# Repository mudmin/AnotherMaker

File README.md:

# AnotherMaker
This is where I will store code snippets for AnotherMaker Videos

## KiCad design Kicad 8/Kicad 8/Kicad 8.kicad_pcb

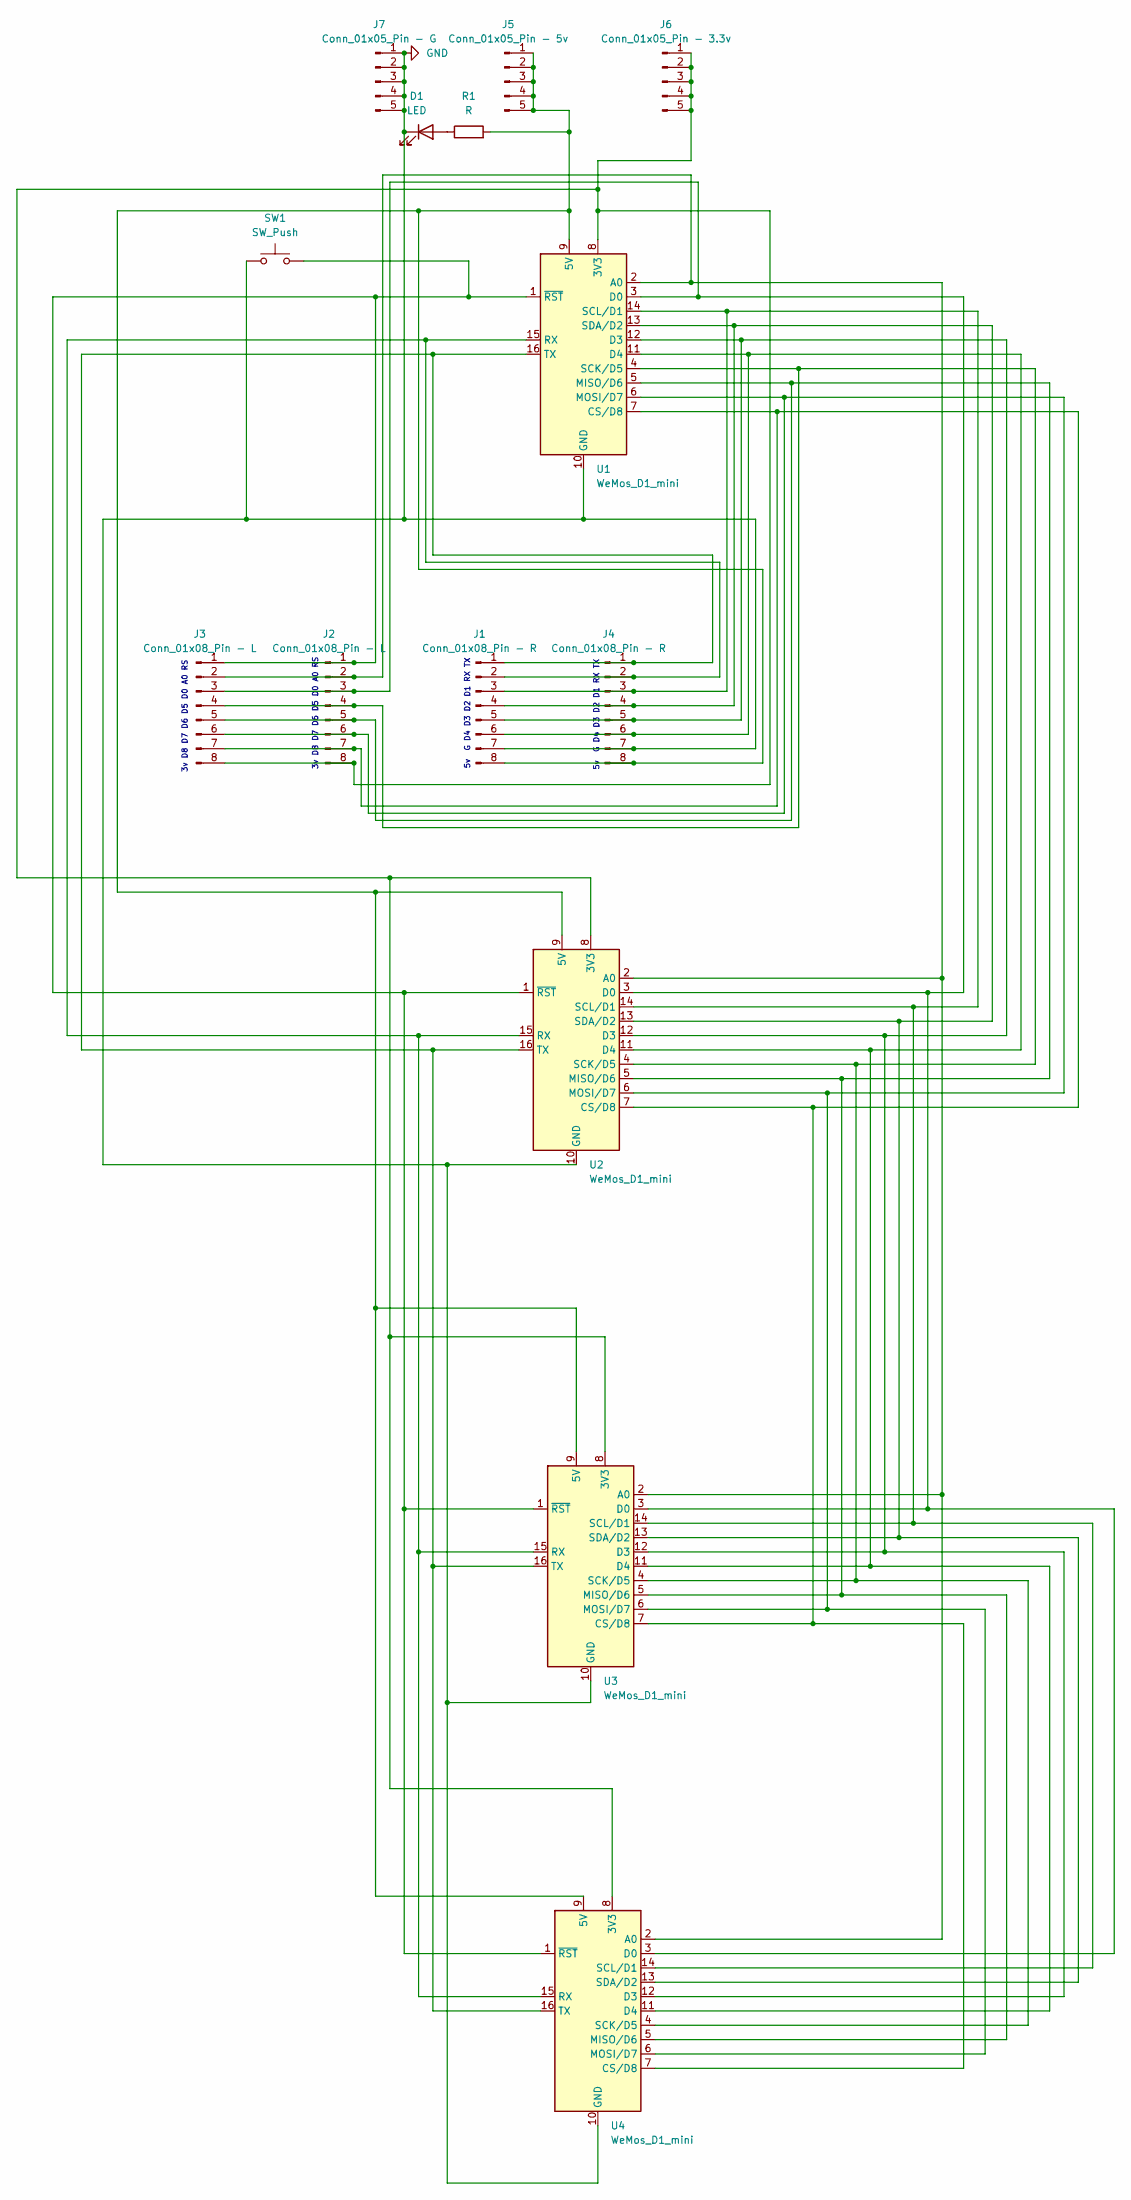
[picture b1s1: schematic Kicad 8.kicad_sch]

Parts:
D1: LED; LED_D3.0mm
J1: Conn_01x08_Pin - R; PinHeader_1x08_P2.54mm_Vertical
J2: Conn_01x08_Pin - L; PinHeader_1x08_P2.54mm_Vertical
J3: Conn_01x08_Pin - L; TerminalBlock_RND_205-00018_1x08_P5.00mm_Horizontal
J4: Conn_01x08_Pin - R; TerminalBlock_RND_205-00018_1x08_P5.00mm_Horizontal
J5: Conn_01x05_Pin - 5v; PinSocket_1x05_P2.54mm_Vertical
J6: Conn_01x05_Pin - 3.3v; PinSocket_1x05_P2.54mm_Vertical
J7: Conn_01x05_Pin - G; PinSocket_1x05_P2.54mm_Vertical
R1: R; R_Axial_DIN0207_L6.3mm_D2.5mm_P7.62mm_Horizontal
SW1: SW_Push; SW_PUSH_6mm_H5mm
U1, U2, U3, U4: WeMos_D1_mini; WEMOS_D1_mini_light

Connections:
GND: D1.1 (K), J1.7, J4.7, J7.1, J7.2, J7.3, J7.4, J7.5, SW1.1, U1.10 (GND), U2.10 (GND), U3.10 (GND), U4.10 (GND)
unnamed: D1.2 (A), R1.1
unnamed: J1.1, J4.1, U1.16 (TX), U2.16 (TX), U3.16 (TX), U4.16 (TX)
unnamed: J1.2, J4.2, U1.15 (RX), U2.15 (RX), U3.15 (RX), U4.15 (RX)
unnamed: J1.3, J4.3, U1.14 (SCL/D1), U2.14 (SCL/D1), U3.14 (SCL/D1), U4.14 (SCL/D1)
unnamed: J1.4, J4.4, U1.13 (SDA/D2), U2.13 (SDA/D2), U3.13 (SDA/D2), U4.13 (SDA/D2)
unnamed: J1.5, J4.5, U1.12 (D3), U2.12 (D3), U3.12 (D3), U4.12 (D3)
unnamed: J1.6, J4.6, U1.11 (D4), U2.11 (D4), U3.11 (D4), U4.11 (D4)
unnamed: J1.8, J4.8, J5.1, J5.2, J5.3, J5.4, J5.5, R1.2, U1.9 (5V), U2.9 (5V), U3.9 (5V), U4.9 (5V)
unnamed: J2.1, J3.1, SW1.2, U1.1 (~RST), U2.1 (~RST), U3.1 (~RST), U4.1 (~RST)
unnamed: J2.2, J3.2, U1.2 (A0), U2.2 (A0), U3.2 (A0), U4.2 (A0)
unnamed: J2.3, J3.3, U1.3 (D0), U2.3 (D0), U3.3 (D0), U4.3 (D0)
unnamed: J2.4, J3.4, U1.4 (SCK/D5), U2.4 (SCK/D5), U3.4 (SCK/D5), U4.4 (SCK/D5)
unnamed: J2.5, J3.5, U1.5 (MISO/D6), U2.5 (MISO/D6), U3.5 (MISO/D6), U4.5 (MISO/D6)
unnamed: J2.6, J3.6, U1.6 (MOSI/D7), U2.6 (MOSI/D7), U3.6 (MOSI/D7), U4.6 (MOSI/D7)
unnamed: J2.7, J3.7, U1.7 (CS/D8), U2.7 (CS/D8), U3.7 (CS/D8), U4.7 (CS/D8)
unnamed: J2.8, J3.8, J6.1, J6.2, J6.3, J6.4, J6.5, U1.8 (3V3), U2.8 (3V3), U3.8 (3V3), U4.8 (3V3)

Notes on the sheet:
3v D8 D7 D6 D5 D0 A0 RS
5v G D4 D3 D2 D1 RX TX

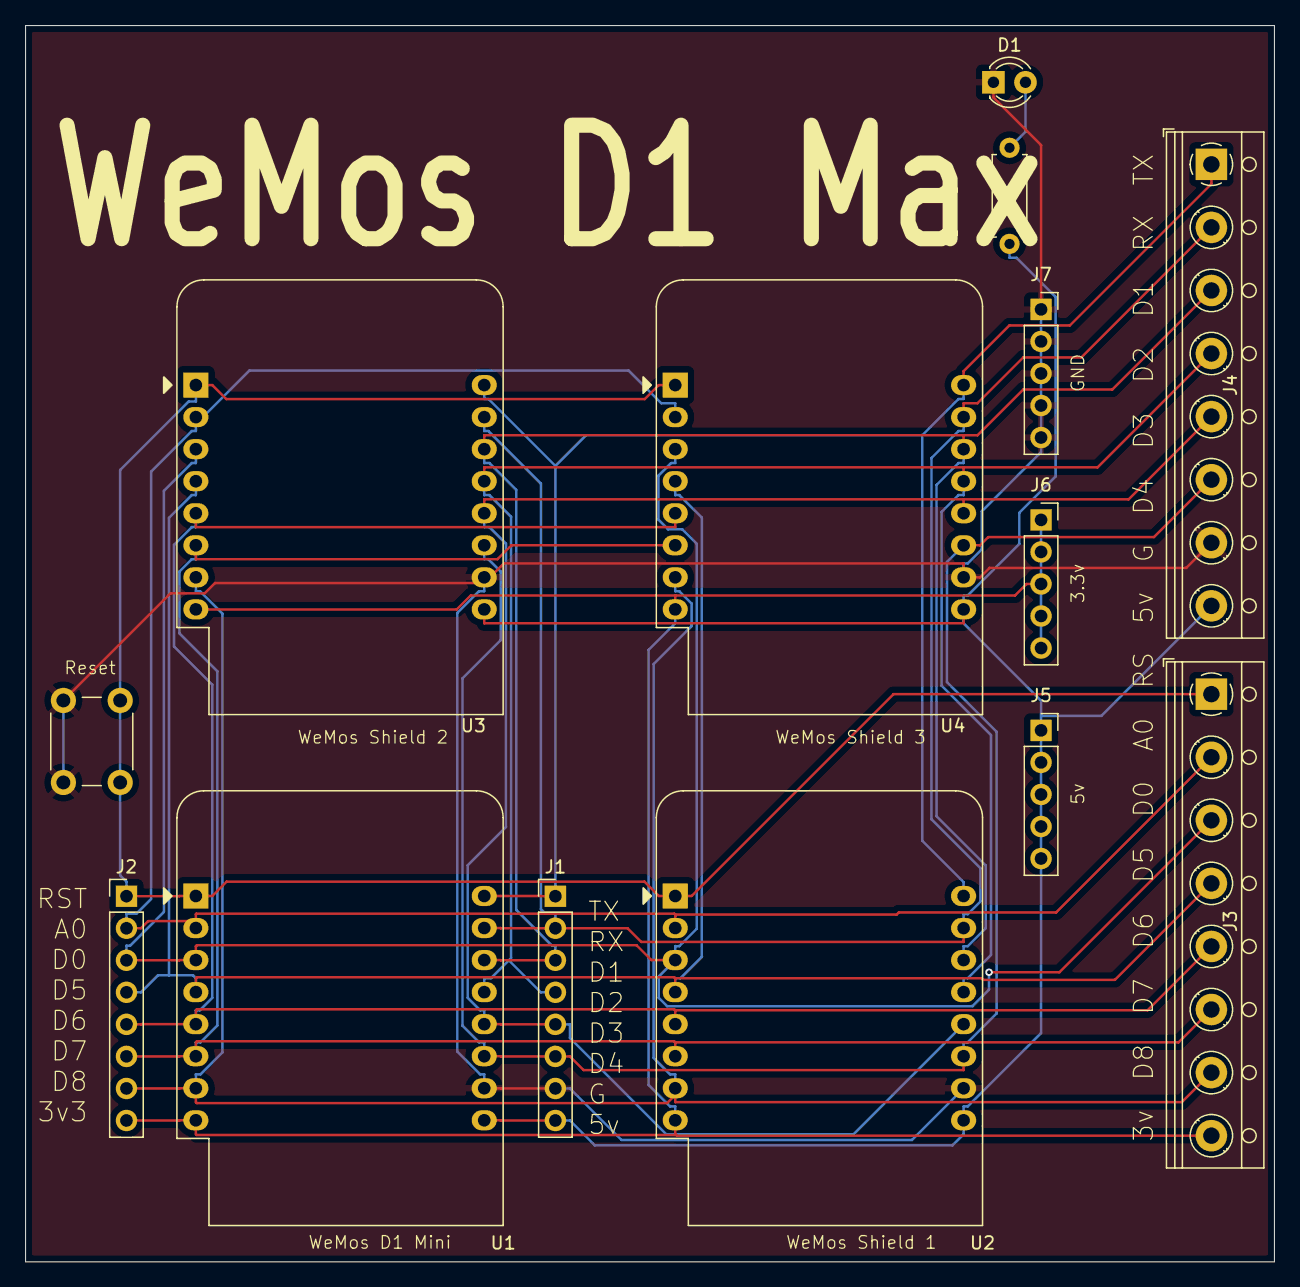
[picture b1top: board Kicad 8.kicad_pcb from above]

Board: 2 copper layers, 99.0 x 98.0 mm, 14 parts (0 on the bottom side), 17 nets.

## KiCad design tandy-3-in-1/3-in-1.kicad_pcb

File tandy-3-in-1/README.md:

# Credit where credit is due
This is forked from https://github.com/rkrenicki/Tandy-EX-HX-3in1 and this repo is primarily here in case his goes away for some reason.

# Tandy 1000 EX/HX 3-in-1 Expansion Board

This is a single expansion board designed for the Tandy 1000 EX and HX computers, to include the following upgrades:

* 640KB Base System Memory
* 96KB Upper Memory
* 16550-based DE9 Serial RS232 Port
* XT-IDE based CompactFlash "Hard Drive"

## Prerequisites

This board is for the Tandy 1000EX and 1000HX computers only.  It will not work in any other computer model as it is.
You must remove any expansion cards already in the computer, this is designed to be a single-board upgrade and has no provisions to allow for any other expansion cards.

## Installing

This board plugs into the Tandy PLUS interface, and takes up "Slot 2" on the rear of the computer.  Please be careful to align the PLUS bus connector before pushing down, to avoid bending pins on the computer.  Secure the backplate to the computer with two screws.
The IDE BIOS will automatically start and boot directly to the CF card on 1000EX machines.   1000HX loads a boot menu by default, and you will need to press F4 to load the IDE BIOS.  If you want to bypass the Tandy DOS ROM and boot menu, run "SETUPHX" and change the "Primary Start-up Device" to "DISK" and press F1 to save.

## Technical Details

This board has no configuration jumpers and is designed to be plug-and-play.  The only jumper is to enable programming the ROM.  Install the jumper to flash the XT-IDE BIOS, otherwise the jumper should be removed.  All assembled boards and kits sold by me come with a pre-programmed ROM, and this jumper should be left empty.

The board is hardwired with these memory locations/ports:
```
SRAM:  0x0000-0x5FFF, 0xC800-0xDFFF
UART:  0x3F8, IRQ 4
IDE:   0x300
ROM:   0xC000-0xC7FF
```

## Assembly Notes
All functions of the board are independent, no parts are shared between functions.  If you do not want to use a specific function, you can safely omit any parts referenced with the function in the name (such as "232" for RS232).

Recommended assembly order: (Shortest to tallest)
* 1  - Resistors (R1-R3, R4 for v1.8+)
* 2  - Bypass Capacitors (C1-C16, only noted as "0.1uF" on the boards)
* 3  - 74 series Chips (U1-4, U6-7, U9, U11-13)
* 4  - ROM Socket (U5 Socket)
* 5  - SRAM Chip (U10)
* 6  - Oscillator (OSC1)
* 7  - UART Socket (U8 Socket)  - Pay very special attention to the orientation!  See note below.
* 8  - Connectors (BUS1, CF-J1, CF-J2, 232-P2)
* 8a - Bodge Resistor on rear of board.  (Only for Version 1.7a boards)
* 9 -  ROM and UART chips into their sockets.
* 10  - CF Adapter
* 11 - Backplate

NOTE:  Please take careful note of part orientation.  To optimize some trace routing, not all chips are oriented in the same direction.  232-U6, 232-U8, and RAM-U11 are all opposite oritentation than the other horizontal chips.  Installing these backwards will destroy the chips.   Pay special attention to 232-U8's socket, it must be installed with the "Pin 1 Arrow" installed facing towards the left of the board.  232-OSC1 is installed "upside down", with the squared corner facing the upper right.

## Bill of Materials
|Quantity |Ref(s)        |Mouser Part Number  |Digikey Part Number |Description                                                     
|-----|--------------|--------------------|--------------------|----------------------------------------------------------------
| 1   |BUS1          |200-CES13101SD<br><i><b>See Note2 Below</i>|SAM1084-31-ND<br><i><b>See Note2 Below</i>|2x31 2.54mm Header Socket
| 1   |CF-J1         |517-8540-4500PL| |2x20 2.54mm Header Socket, 11mm height.
| 4   |R1 through R4 |603-CFR-12JT-52-10K | |10kOhm Resistor
| 16  |C1 through C16|594-K104M15X7RF53L2 | |0.1uF Multilayer Ceramic Capacitor, 2.5mm Lead Spacing
| 1   |CP1           |647-RNU1C101MDS1    | |100uF 16V Polymer or Electrolytic Capacitor, 2.5mm Lead Spacing
| 1   |232-OSC1      |774-MXO45HS-3C-1.8  |110-MXO45HS-3C-1M843200-ND |1.8432Mhz 1/2-size Oscillator
| 1   |232-P2        |806-K22X-E9P-N-99   |2092-K22X-E9P-N-ND      |DE9 Male Right Angle Connector  
| 2   |232-P2 Screw  |571-5207953-3       |SFSO4401NR-ND           |Jackscrew for DE9 connector
| 1   |232-U6        |595-GD75232N        |296-GD75232N-ND         |GD75232N RS232 Driver
| 2   |232-U7, 232-U9|595-SN74LS138N      |296-1639-5-ND           |74LS138 3-to-8 Line Demux
| 1   |232-U8        |701-ST16C550CJ44TR-F|1016-1259-5-ND          |16550/16C550 UART in PLCC-44 Package
| 1   |232-U8 Socket |517-8444-11B1-RK-TP |3M4411B1-ND             |PLCC-44 Through Hole Socket
| 1   |CF-J2         |200-CES10101TD      | |1x2 2.54mm Header Socket
| 1   |CF-U1         |595-SN74LS139AN     |296-1640-5-ND           |74LS139 Dual 2-to-4 Demux
| 2   |CF-U2, ROM-U4 |595-SN74LS688N<br> or 595-SN74F521N      |296-1667-5-ND          |74LS688 or 74F521 8-bit Comparator
| 2   |CF-U3, RAM-U11|595-SN74LS245N      |296-1655-5-ND           |74LS245 Tri-state Bus Transciever
| 1   |RAM-U10       |913-AS6C4008-55PCN  |1450-1027-ND            |AS6C4008-55PCN 4mbit (512k x 8) Static RAM
| 1   |RAM-U12       |595-SN74LS00N       |296-1626-ND             |74LS00 Quad NAND Gate
| 1   |RAM-U13       |595-SN74LS32N       |296-1658-5-ND           |74LS32 Quad OR Gate
| 1   |ROM-U5        |556-AT28C64B15PU    |AT28C64B-15PU-ND        |28C64 64k x 8 EEPROM
| 1   |ROM-U5 Socket |517-4828-6000-CP    |ED3052-5-ND             |28-pin Wide DIP Socket
| 1   |CF-IDE Adapter|n/a                 |n/a                     |CF to IDE Adapter from eBay or AliExpress (See note below)

Note:	All 74LSxx series logic ICs can be substituted with any family with "LS" or "T" in the name, such as ALS, ACT, AHCT, or HCT among others.

Note2: For the BUS1 Connectors, I have many of these left over from my last order of custom connectors.   You can buy them for $1/ea plus shipping.  Even for one, it is far cheaper than the $13 that Mouser wants.   Please email tandy.3in1@gmail.com to order.
## BIOS

This board uses the XT-IDE Universal BIOS.  I have included pre-configured images for 2.0.0B3 r602 (latest version as of the time of writing this).  The 3in1BIOS-8088.zip will work on any EX or HX computer, and is the version that I preload on assembled boards and kits.   I have also included a V20 Enhanced version for any EX/HX that has an NEC V20 (or clone) installed.   This enhanced version will roughly double your disk speed, but only works on V20 machines.

## CF-IDE Adapter

This board is designed a specific version of a CF-IDE adapter.  They are widely available on eBay and AliExpress.  It bears the mark of "IDE to CF Ver.D2".  It can generally be identified by the metal cover over the CF card connector.   I do not have a link to any one specific vendor or listing, but if the adapter includes the metal backplate and has a metal cover over the CF slot, then it should be correct.

The CF adapter does also need a few modifications, please refer to the "IDE Adapter Modifications.pdf" for details.  It also has photos of the adapter for reference to buy the proper adapter.

If you have any questions, feel free to join the Discord server below and ask in the #tandy-3in1-support channel.

## Support Discord

I have started a Discord server for more real-time technical support, as well as discussion for my various projects in progress.   You can follow this link to join:  https://discord.gg/QmFssyXnQt

## Built With

* [KiCAD EDA](http://www.kicad.org/)

## Authors

* **Rob Krenicki** - [rkrenicki](https://github.com/rkrenicki)

## License

This project is licensed under the Creative Commons - Attribution - ShareAlike 3.0 License

## Attribution

This board was derrived from works by, uses design elements from, or contains sofware writen by the following:
* Sergey Kiselev (http://www.malinov.com/Home/sergeys-projects)
* James Pearce (https://www.lo-tech.co.uk/)
* Adrian Black (https://www.youtube.com/user/craig1black/featured)
* Jacob Dorne of Monotech PCs (https://monotech.fwscart.com/)
* XTIDE Universal BIOS Team (http://www.xtideuniversalbios.org/)

## README TO-DO
* Assembly Instructions

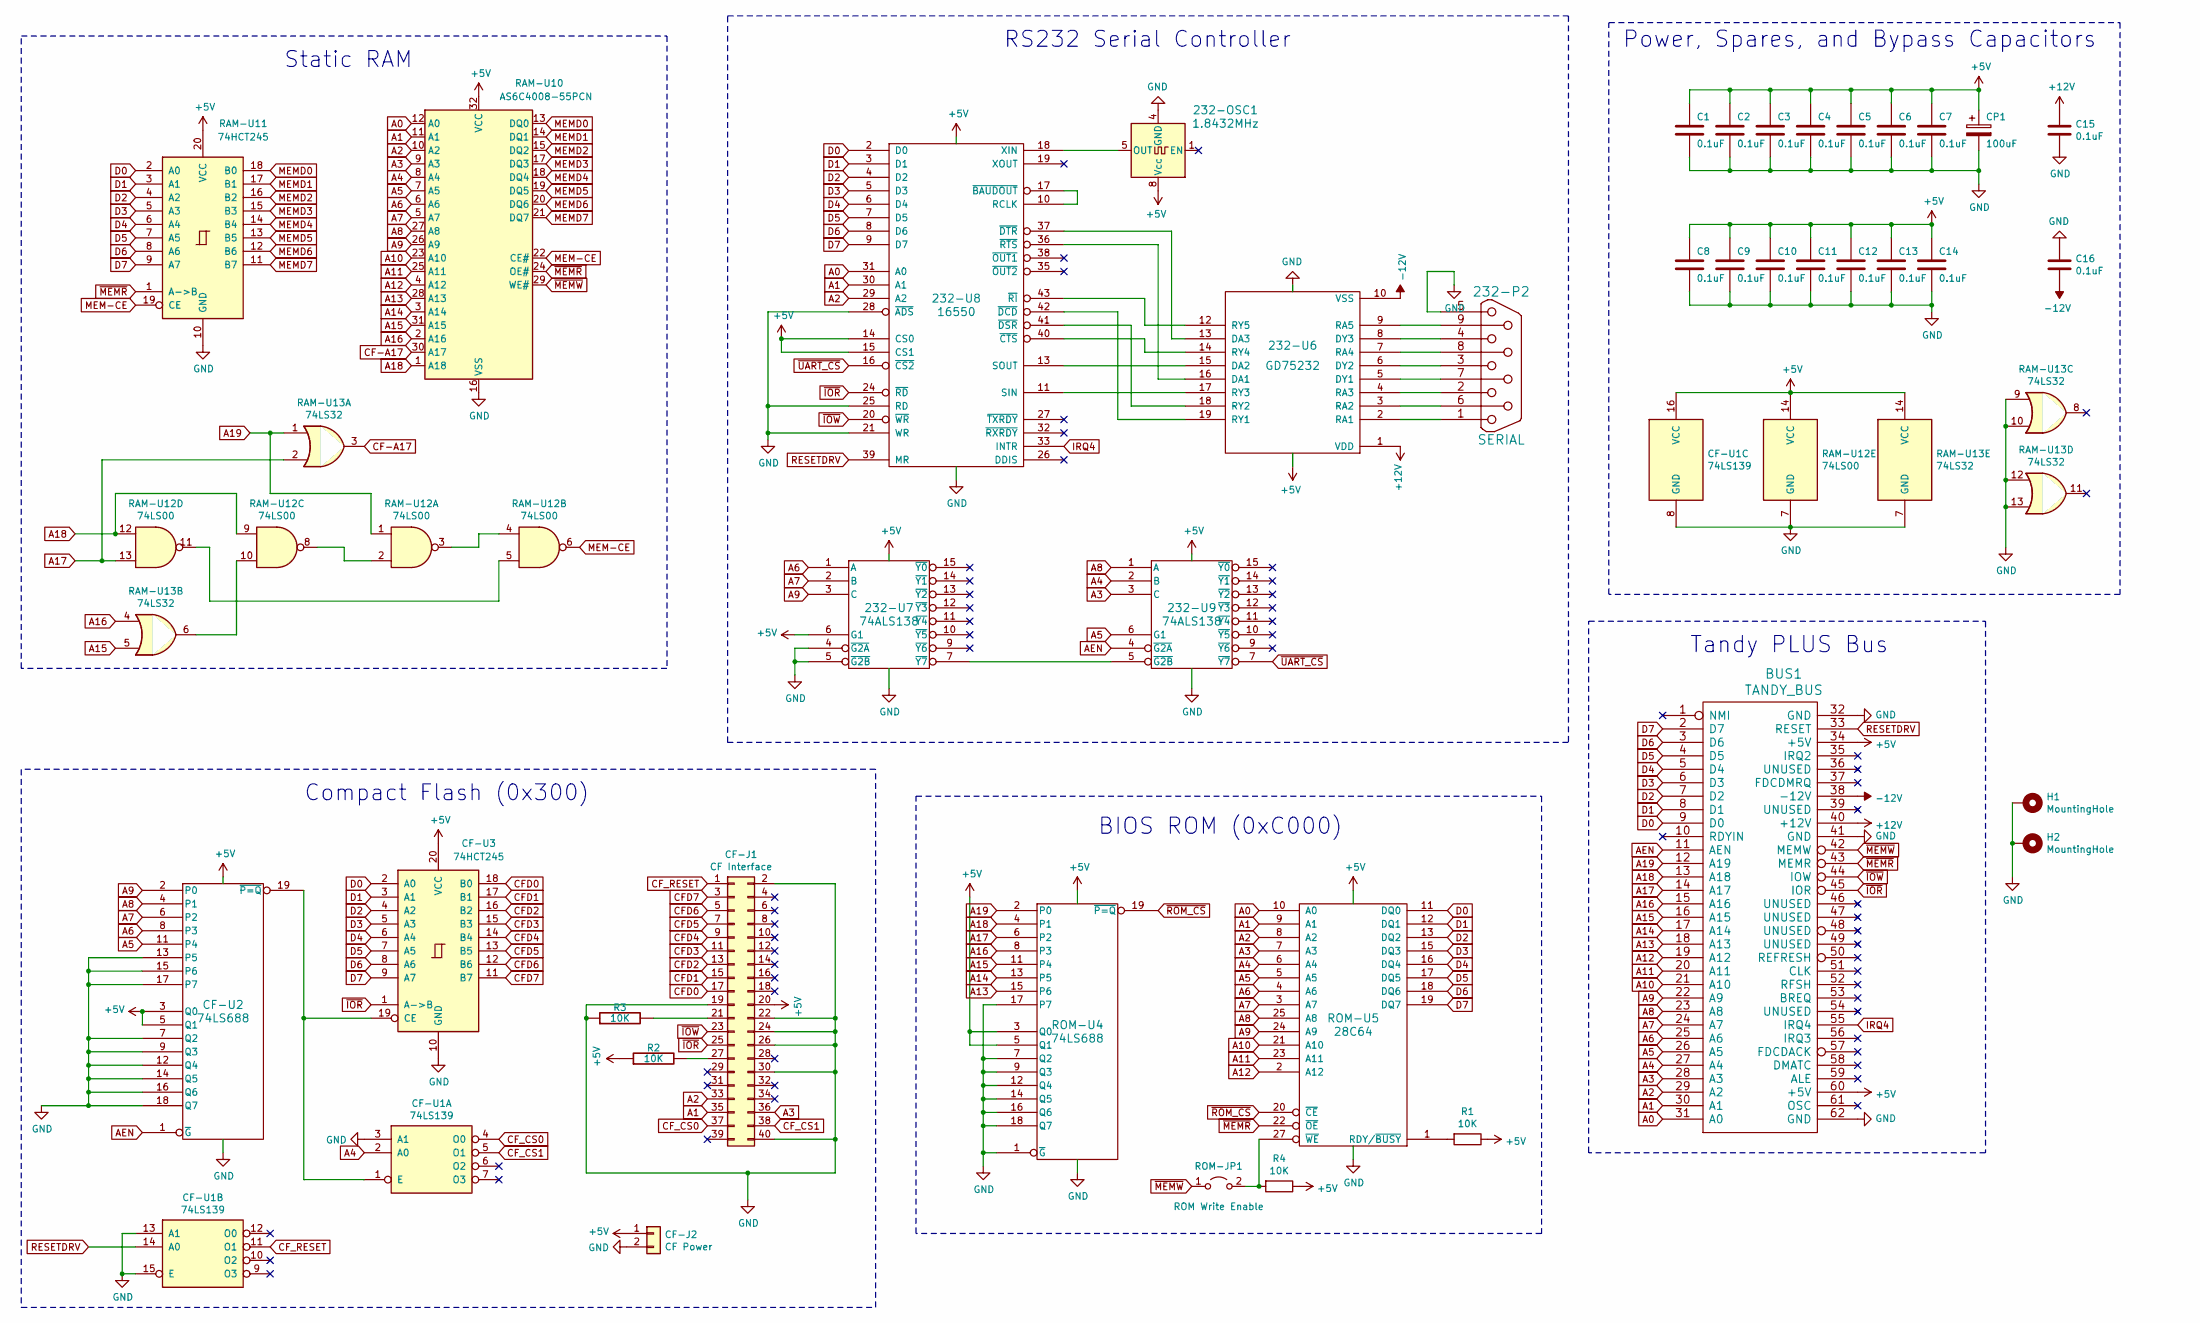
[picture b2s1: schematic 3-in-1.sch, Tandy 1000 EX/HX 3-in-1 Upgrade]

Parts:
232-OSC1: 1.8432MHz; Oscillator_DIP-8
232-P2: SERIAL; DSUB-9_Male_Horizontal_P2.77x2.84mm_EdgePinOffset7.70mm_Hou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
232-U6: GD75232; DIP-20_W7.62mm
232-U7, 232-U9: 74ALS138; DIP-16_W7.62mm
232-U8: 16550; PLCC-44_THT-Socket
BUS1: TANDY_BUS; TANDY-PLUS-BUS
C1, C2, C3, C4, C5, C6, C7, C8, C9, C10, C11, C12, C13, C14, C15, C16: 0.1uF; C_Disc_D3.0mm_W2.0mm_P2.50mm
CF-J1: CF Interface; PinSocket_2x20_P2.54mm_Vertical
CF-J2: CF Power; PinSocket_1x02_P2.54mm_Vertical
CF-U1: 74LS139; DIP-16_W7.62mm
CF-U2: 74LS688; DIP-20_W7.62mm
CF-U3: 74HCT245; DIP-20_W7.62mm
CP1: 100uF; CP_Radial_D5.0mm_P2.50mm
H1, H2: MountingHole; MountingHole_2.7mm_M2.5_ISO7380_Pad
R1, R2, R3, R4: 10K; R_Axial_DIN0204_L3.6mm_D1.6mm_P5.08mm_Horizontal
RAM-U10: AS6C4008-55PCN; DIP-32_W15.24mm
RAM-U11: 74HCT245; DIP-20_W7.62mm
RAM-U12: 74LS00; DIP-14_W7.62mm
RAM-U13: 74LS32; DIP-14_W7.62mm
ROM-JP1: ROM Write Enable; PinHeader_1x02_P2.54mm_Vertical
ROM-U4: 74LS688; DIP-20_W7.62mm
ROM-U5: 28C64; DIP-28_W15.24mm

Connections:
+5V: 232-OSC1.8 (Vcc), 232-U6.20 (VCC), 232-U7.6 (G1), 232-U7.16 (VCC), 232-U8.14 (CS0), 232-U8.15 (CS1), 232-U8.44 (VCC), 232-U9.16 (VCC), BUS1.34 (+5V), BUS1.60 (+5V), C1.1, C2.1, C3.1, C4.1, C5.1, C6.1, C7.1, C8.1, C9.1, C10.1, C11.1, C12.1, C13.1, C14.1, CF-J1.20, CF-J2.1, CF-U1.16 (VCC), CF-U2.3 (Q0), CF-U2.5 (Q1), CF-U2.20 (VCC), CF-U3.20 (VCC), CP1.1, R1.1, R2.1, R4.1, RAM-U10.32 (VCC), RAM-U11.20 (VCC), RAM-U12.14 (VCC), RAM-U13.14 (VCC), ROM-U4.3 (Q0), ROM-U4.5 (Q1), ROM-U4.20 (VCC), ROM-U5.28 (VCC)
+12V: 232-U6.1 (VDD), BUS1.40 (+12V), C15.1
-12V: 232-U6.10 (VSS), BUS1.38 (-12V), C16.2
A0: 232-U8.31 (A0), BUS1.31 (A0), RAM-U10.12 (A0), ROM-U5.10 (A0)
A1: 232-U8.30 (A1), BUS1.30 (A1), CF-J1.35, RAM-U10.11 (A1), ROM-U5.9 (A1)
A2: 232-U8.29 (A2), BUS1.29 (A2), CF-J1.33, RAM-U10.10 (A2), ROM-U5.8 (A2)
A3: 232-U9.3 (C), BUS1.28 (A3), CF-J1.36, RAM-U10.9 (A3), ROM-U5.7 (A3)
A4: 232-U9.2 (B), BUS1.27 (A4), CF-U1.2 (A0), RAM-U10.8 (A4), ROM-U5.6 (A4)
A5: 232-U9.6 (G1), BUS1.26 (A5), CF-U2.11 (P4), RAM-U10.7 (A5), ROM-U5.5 (A5)
A6: 232-U7.1 (A), BUS1.25 (A6), CF-U2.8 (P3), RAM-U10.6 (A6), ROM-U5.4 (A6)
A7: 232-U7.2 (B), BUS1.24 (A7), CF-U2.6 (P2), RAM-U10.5 (A7), ROM-U5.3 (A7)
A8: 232-U9.1 (A), BUS1.23 (A8), CF-U2.4 (P1), RAM-U10.27 (A8), ROM-U5.25 (A8)
A9: 232-U7.3 (C), BUS1.22 (A9), CF-U2.2 (P0), RAM-U10.26 (A9), ROM-U5.24 (A9)
A10: BUS1.21 (A10), RAM-U10.23 (A10), ROM-U5.21 (A10)
A11: BUS1.20 (A11), RAM-U10.25 (A11), ROM-U5.23 (A11)
A12: BUS1.19 (A12), RAM-U10.4 (A12), ROM-U5.2 (A12)
A13: BUS1.18 (A13), RAM-U10.28 (A13), ROM-U4.15 (P6)
A14: BUS1.17 (A14), RAM-U10.3 (A14), ROM-U4.13 (P5)
A15: BUS1.16 (A15), RAM-U10.31 (A15), RAM-U13.5, ROM-U4.11 (P4)
A16: BUS1.15 (A16), RAM-U10.2 (A16), RAM-U13.4, ROM-U4.8 (P3)
A17: BUS1.14 (A17), RAM-U12.13, RAM-U13.2, ROM-U4.6 (P2)
A18: BUS1.13 (A18), RAM-U10.1 (A18), RAM-U12.9, RAM-U12.12, ROM-U4.4 (P1)
A19: BUS1.12 (A19), RAM-U12.1, RAM-U13.1, ROM-U4.2 (P0)
AEN: 232-U9.4 (~G2A), BUS1.11 (AEN), CF-U2.1 (~G)
CF-A17: RAM-U10.30 (A17), RAM-U13.3
CFD0: CF-J1.17, CF-U3.18 (B0)
CFD1: CF-J1.15, CF-U3.17 (B1)
CFD2: CF-J1.13, CF-U3.16 (B2)
CFD3: CF-J1.11, CF-U3.15 (B3)
CFD4: CF-J1.9, CF-U3.14 (B4)
CFD5: CF-J1.7, CF-U3.13 (B5)
CFD6: CF-J1.5, CF-U3.12 (B6)
CFD7: CF-J1.3, CF-U3.11 (B7)
CF_CS0: CF-J1.37, CF-U1.4 (O0)
CF_CS1: CF-J1.38, CF-U1.5 (O1)
CF_RESET: CF-J1.1, CF-U1.11 (O1)
D0: 232-U8.2 (D0), BUS1.9 (D0), CF-U3.2 (A0), RAM-U11.2 (A0), ROM-U5.11 (DQ0)
D1: 232-U8.3 (D1), BUS1.8 (D1), CF-U3.3 (A1), RAM-U11.3 (A1), ROM-U5.12 (DQ1)
D2: 232-U8.4 (D2), BUS1.7 (D2), CF-U3.4 (A2), RAM-U11.4 (A2), ROM-U5.13 (DQ2)
D3: 232-U8.5 (D3), BUS1.6 (D3), CF-U3.5 (A3), RAM-U11.5 (A3), ROM-U5.15 (DQ3)
D4: 232-U8.6 (D4), BUS1.5 (D4), CF-U3.6 (A4), RAM-U11.6 (A4), ROM-U5.16 (DQ4)
D5: 232-U8.7 (D5), BUS1.4 (D5), CF-U3.7 (A5), RAM-U11.7 (A5), ROM-U5.17 (DQ5)
D6: 232-U8.8 (D6), BUS1.3 (D6), CF-U3.8 (A6), RAM-U11.8 (A6), ROM-U5.18 (DQ6)
D7: 232-U8.9 (D7), BUS1.2 (D7), CF-U3.9 (A7), RAM-U11.9 (A7), ROM-U5.19 (DQ7)
GND: 232-OSC1.4 (GND), 232-P2.0, 232-P2.5, 232-U6.11 (GND), 232-U7.4 (~G2A), 232-U7.5 (~G2B), 232-U7.8 (GND), 232-U8.21 (WR), 232-U8.22 (GND), 232-U8.25 (RD), 232-U8.28 (~ADS), 232-U9.8 (GND), BUS1.32 (GND), BUS1.41 (GND), BUS1.62 (GND), C1.2, C2.2, C3.2, C4.2, C5.2, C6.2, C7.2, C8.2, C9.2, C10.2, C11.2, C12.2, C13.2, C14.2, C15.2, C16.1, CF-J1.2, CF-J1.19, CF-J1.22, CF-J1.24, CF-J1.26, CF-J1.30, CF-J1.40, CF-J2.2, CF-U1.3 (A1), CF-U1.8 (GND), CF-U1.13 (A1), CF-U1.15 (E), CF-U2.7 (Q2), CF-U2.9 (Q3), CF-U2.10 (GND), CF-U2.12 (Q4), CF-U2.13 (P5), CF-U2.14 (Q5), CF-U2.15 (P6), CF-U2.16 (Q6), CF-U2.17 (P7), CF-U2.18 (Q7), CF-U3.10 (GND), CP1.2, H1.1, H2.1, R3.1, RAM-U10.16 (VSS), RAM-U11.10 (GND), RAM-U12.7 (GND), RAM-U13.7 (GND), RAM-U13.9, RAM-U13.10, RAM-U13.12, RAM-U13.13, ROM-U4.1 (~G), ROM-U4.7 (Q2), ROM-U4.9 (Q3), ROM-U4.10 (GND), ROM-U4.12 (Q4), ROM-U4.14 (Q5), ROM-U4.16 (Q6), ROM-U4.17 (P7), ROM-U4.18 (Q7), ROM-U5.14 (GND)
IRQ4: 232-U8.33 (INTR), BUS1.55 (IRQ4)
MEM-CE: RAM-U10.22 (CE#), RAM-U11.19 (CE), RAM-U12.6
MEMD0: RAM-U10.13 (DQ0), RAM-U11.18 (B0)
MEMD1: RAM-U10.14 (DQ1), RAM-U11.17 (B1)
MEMD2: RAM-U10.15 (DQ2), RAM-U11.16 (B2)
MEMD3: RAM-U10.17 (DQ3), RAM-U11.15 (B3)
MEMD4: RAM-U10.18 (DQ4), RAM-U11.14 (B4)
MEMD5: RAM-U10.19 (DQ5), RAM-U11.13 (B5)
MEMD6: RAM-U10.20 (DQ6), RAM-U11.12 (B6)
MEMD7: RAM-U10.21 (DQ7), RAM-U11.11 (B7)
unnamed: 232-OSC1.5 (OUT), 232-U8.18 (XIN)
unnamed: 232-P2.1, 232-U6.2 (RA1)
unnamed: 232-P2.2, 232-U6.4 (RA3)
unnamed: 232-P2.3, 232-U6.6 (DY2)
unnamed: 232-P2.4, 232-U6.8 (DY3)
unnamed: 232-P2.6, 232-U6.3 (RA2)
unnamed: 232-P2.7, 232-U6.5 (DY1)
unnamed: 232-P2.8, 232-U6.7 (RA4)
unnamed: 232-P2.9, 232-U6.9 (RA5)
unnamed: 232-U6.12 (RY5), 232-U8.43 (~RI)
unnamed: 232-U6.13 (DA3), 232-U8.37 (~DTR)
unnamed: 232-U6.14 (RY4), 232-U8.40 (~CTS)
unnamed: 232-U6.15 (DA2), 232-U8.13 (SOUT)
unnamed: 232-U6.16 (DA1), 232-U8.36 (~RTS)
unnamed: 232-U6.17 (RY3), 232-U8.11 (SIN)
unnamed: 232-U6.18 (RY2), 232-U8.41 (~DSR)
unnamed: 232-U6.19 (RY1), 232-U8.42 (~DCD)
unnamed: 232-U7.7 (~Y7), 232-U9.5 (~G2B)
unnamed: 232-U8.10 (RCLK), 232-U8.17 (~BAUDOUT)
unnamed: CF-J1.21, R3.2
unnamed: CF-J1.27, R2.2
unnamed: CF-U1.1 (E), CF-U2.19 (~P=Q), CF-U3.19 (CE)
unnamed: R1.2, ROM-U5.1 (RDY/~BUSY)
unnamed: R4.2, ROM-JP1.2 (B), ROM-U5.27 (~WE)
unnamed: RAM-U12.2, RAM-U12.8
unnamed: RAM-U12.3, RAM-U12.4
unnamed: RAM-U12.10, RAM-U13.6
unnamed: RAM-U12.5, RAM-U12.11
RESETDRV: 232-U8.39 (MR), BUS1.33 (RESET), CF-U1.14 (A0)
~IOR: 232-U8.24 (~RD), BUS1.45 (IOR), CF-J1.25, CF-U3.1 (A->B)
~IOW: 232-U8.20 (~WR), BUS1.44 (IOW), CF-J1.23
~MEMR: BUS1.43 (MEMR), RAM-U10.24 (OE#), RAM-U11.1 (A->B), ROM-U5.22 (~OE)
~MEMW: BUS1.42 (MEMW), RAM-U10.29 (WE#), ROM-JP1.1 (A)
~ROM_CS: ROM-U4.19 (~P=Q), ROM-U5.20 (~CE)
~UART_CS: 232-U8.16 (~CS2), 232-U9.7 (~Y7)

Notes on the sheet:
RS232 Serial Controller
BIOS ROM (0xC000)
Power, Spares, and Bypass Capacitors
Tandy PLUS Bus
Static RAM
Compact Flash (0x300)

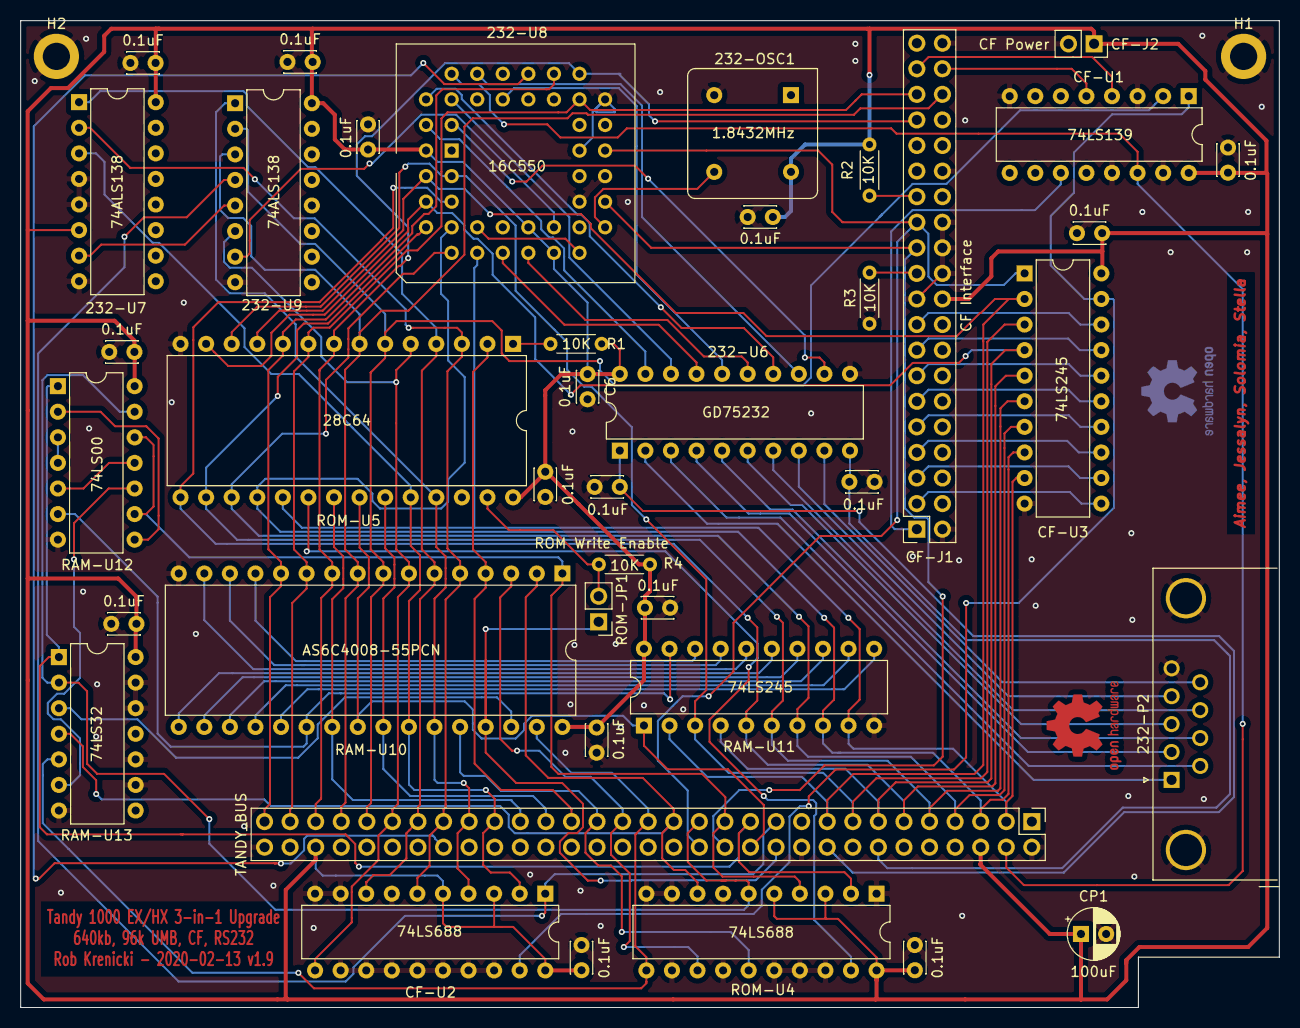
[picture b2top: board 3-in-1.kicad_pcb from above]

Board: 2 copper layers, 125.0 x 98.0 mm, 42 parts (0 on the bottom side), 90 nets.

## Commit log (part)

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2019-08-17 5 Practical Uses for Node-Red on Android
2019-08-17 Global Variables in Node Red
2019-08-19 Play MP3s in PHP
2019-08-19 Added additonal comments to mp3
2019-09-01 soldering perf board
2019-09-03 API Relays and Examples
2019-09-06 ir-rf
2019-09-19 Added Arduino Gameshow Buzzer
2019-09-19 Added a little visualization
2019-10-20 olimex
2020-01-11 Arduino Shooting Gallery - Intermediate Project
2020-02-24 Blink without Delay
2020-03-15 Cash Reader
2020-03-15 rigged-o-fortune
2020-05-16 Smart(er) doorbell part 1
2020-05-23 Quack Attack
2020-05-23 Smart Doorbell ESP32
2020-05-28 ds18b20
2020-05-28 Esp32 joke phone
2020-06-14 Youtube Notifier
2020-06-15 Arduino Escape Room
2020-06-18 Soundbar fixer
2020-06-18 Increased time to 30 mins
2020-06-22 refactoring time
2020-07-26 RGBDuino Fork and Reorg
2020-07-26 Additional comments and 3 new examples
2020-07-26 StreamArray :)
2020-07-26 Forgot to add photo editor
2020-07-28 Added simple version of streaming deck
2020-08-07 Traffic Light and water quality videos
2020-08-07 self contained gameshow
2020-08-20 OpenCanary
2020-08-22 Canary zero
2020-08-23 additonal opencanary notes
2020-10-03 IT Waker Upper
2020-10-06 added ring history to dashboard and auto turn off of buzzer
2020-10-07 Quick itwu dashboard responsive fix
2020-12-21 latest videos
2020-12-22 latest videos
2021-01-02 latest wibu - will it blow up
2021-01-05 Added Important Note for Ubuntu Setup
    Added a note to rename the /.openconary.conf for Ubuntu to resolve a startup issue. I installed OpenCanary on Ubuntu 20.04.1 LTS with Python3.
2021-01-11 splitting barcode by newline
2021-01-22 Raspberry Pi Camera misc info
2021-01-22 Getting started guide
2021-01-31 New TV
2021-02-09 37 sensors 1 arduino
2021-03-11 Project legacy
2021-03-20 Sim7000g
2021-03-22 Cayenne Lilygo
2021-03-25 Pi cooling test
2021-04-19 Gotek Drive bay and modification resources
2021-05-15 energyduino
2021-07-02 esp32 watch
2021-07-07 Hyperbowl code and laser files
2021-07-07 Mission Control Button Grid
2021-07-07 Button text wiring list for Button grid
2021-07-22 do not touch button
2021-07-23 raspad lightburn file
2021-07-28 ESP32 TV B Gone Watch
2021-10-23 Arduino lidar
2021-10-23 Lidar graphic
2021-12-18 Arduino wind speed
2021-12-20 Esp32 prank
2022-03-15 EPROM Software
2022-03-28 Arduino EEPROM Torture
2022-03-28 forgot an =
2022-04-09 Updated and cleaned up
    added parameters, cleaned up execution, added more detailed serial return, increased serial baud rate.
2022-04-16 youtube notifier node-red
2022-06-22 Ultimate gameshow
2022-07-01 PCB Projects
2022-07-15 Olimex ESP32-POE-ISO
2022-07-15 olimex sample code
2022-07-30 Common component values for labels and organizing
2022-10-23 pi christmas tree
2022-10-29 frehd
2022-10-29 Fred hex and jed files
2022-10-31 Atari
2022-10-31 Latest Frehd
2022-10-31 adding photo
2022-10-31 FreHd Build notes
2022-10-31 3 in 1 notes
2022-11-23 Train led to answer a question in the comments
2023-02-11 retro emulation
2023-02-17 Raw test data for circuit specialists variac
2023-07-06 board holder fusion 360 file credit SimpleElectronics on youtube
2023-08-12 franklin ace 1000
2023-08-12 commit ryzen9
2023-08-23 Cheap yellow display
2023-10-02 The $4 XT-IDE
2023-10-02 video link
2023-12-11 Apple ][
2023-12-31 Gotek Apple II
2024-05-04 Facebook sucks
2024-05-04 FB and YT Suck
2024-05-04 remove blank line
2024-05-04 moving post since this aint userspice and I can't do that.
2024-05-04 New and improved YT Sucks
2024-05-04 fix small formatting issue
2024-05-19 9 pin tester
2024-05-19 added arduino instructions
2024-05-21 incomplete pcbs
2024-05-25 button addon for 9 pin tester
2024-06-02 555 PCB 2
2024-06-09 Kicad
2024-06-29 note changes
2024-06-29 ntoes
2024-07-07 final circuits
2025-01-12 Tandy Terminator and EPROM Booster
2025-01-26 EEPROM booster notes
2025-02-02 Frehd import tool
2025-02-13 lazy kicad
2025-02-13 update maker
2025-02-13 donate link.. You never know
2025-02-16 Lazy Kicad generator can now be extended
2025-02-20 Olimex ethernet diag
2025-02-20 ethernet udp example
2025-05-17 Youtube sucks 2.0
2025-05-18 Tandy 2000 3d designs
2026-04-23 latest yt sucks tool

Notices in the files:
tandy-3-in-1/3-in-1.sch:
OSHW - Creative Commons Attribution ShareAlike 3.0
